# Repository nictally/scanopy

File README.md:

Hello, This is the repository for scanopy a smart air pollution monitoring system.

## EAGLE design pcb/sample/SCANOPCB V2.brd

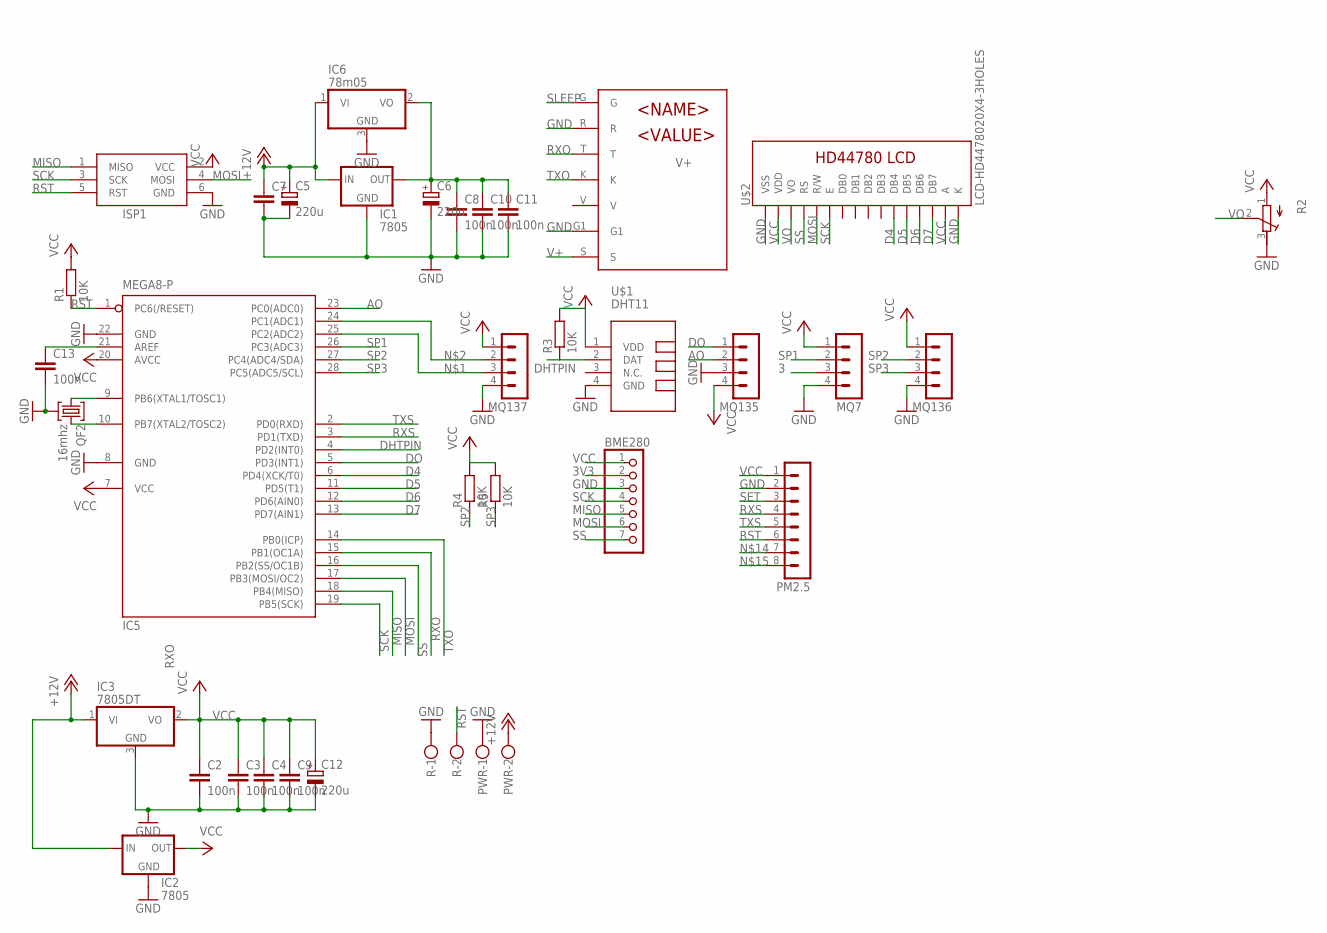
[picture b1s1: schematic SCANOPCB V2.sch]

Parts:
BME280: PINHD-1X7; 1X07
C2, C3, C4, C8, C9, C10, C11, C13: 100n; C1206
C5, C6, C12: 220u; E5-8,5
C7: C-EUC1206; C1206
IC1, IC2: 7805; 78XXL
IC3: 7805DT; TO252
IC5: MEGA8-P; DIL28-3
IC6: 78m05; TO252
ISP1: AVRISP-6; AVRISP
MQ7, MQ135, MQ136, MQ137: MA04-1
PM2.5: MA08-1
PWR: W237-102
QF2: 16mhz; HC49U
R: W237-102
R1, R3, R4, R5: 10K; R1206
R2: R-TRIMM64P; RTRIM64P
SIM7000: SIM7000
U$1: DHT11; TEMP-HUM-SENSOR-DHT11
U$2: LCD-HD4478020X4-3HOLES; LCD-20X4-3HOLES

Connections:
3: MQ7.3
3V3: BME280.2
+12V: C5.+, C7.1, IC1.IN, IC2.IN, IC3.1 (VI), IC6.1 (VI), PWR.2
AO: IC5.23 (PC0(ADC0)), MQ135.2
D4: IC5.6 (PD4(XCK/T0)), U$2.P$11 (DB4)
D5: IC5.11 (PD5(T1)), U$2.P$12 (DB5)
D6: IC5.12 (PD6(AIN0)), U$2.P$13 (DB6)
D7: IC5.13 (PD7(AIN1)), U$2.P$14 (DB7)
DHTPIN: IC5.4 (PD2(INT0)), R3.1, U$1.2 (DAT)
DO: IC5.5 (PD3(INT1)), MQ135.1
GND: BME280.3, C2.2, C3.2, C4.2, C5.-, C6.-, C7.2, C8.2, C9.2, C10.2, C11.2, C12.-, C13.2, IC1.GND, IC2.GND, IC3.3 (GND), IC5.8 (GND), IC5.22 (GND), IC6.3 (GND), ISP1.6 (GND), MQ7.4, MQ135.3, MQ136.4, MQ137.4, PM2.5.2, PWR.1, QF2.2, R.1, R2.3 (E), SIM7000.G1, SIM7000.R, U$1.4 (GND), U$2.P$1 (VSS), U$2.P$16 (K)
MISO: BME280.5, IC5.18 (PB4(MISO)), ISP1.1 (MISO)
MOSI: BME280.6, IC5.17 (PB3(MOSI/OC2)), ISP1.4 (MOSI), U$2.P$5 (R/W)
unnamed: IC5.25 (PC2(ADC2)), MQ137.3
unnamed: IC5.24 (PC1(ADC1)), MQ137.2
unnamed: C13.1, IC5.21 (AREF)
unnamed: IC5.9 (PB6(XTAL1/TOSC1)), QF2.1
unnamed: IC5.10 (PB7(XTAL2/TOSC2)), QF2.3
RST: IC5.1 (PC6(/RESET)), ISP1.5 (RST), PM2.5.6, R.2, R1.1
RXO: IC5.15 (PB1(OC1A)), SIM7000.T
RXS: IC5.3 (PD1(TXD)), PM2.5.4
SCK: BME280.4, IC5.19 (PB5(SCK)), ISP1.3 (SCK), U$2.P$6 (E)
SET: PM2.5.3
SLEEP: SIM7000.G
SP1: IC5.26 (PC3(ADC3)), MQ7.2
SP2: IC5.27 (PC4(ADC4/SDA)), MQ136.2, R4.1
SP3: IC5.28 (PC5(ADC5/SCL)), MQ136.3, R5.1
SS: BME280.7, IC5.16 (PB2(SS/OC1B)), U$2.P$4 (RS)
TXO: IC5.14 (PB0(ICP)), SIM7000.K
TXS: IC5.2 (PD0(RXD)), PM2.5.5
V+: C6.+, C8.1, C10.1, C11.1, IC1.OUT, IC6.2 (VO), SIM7000.S
VCC: BME280.1, C2.1, C3.1, C4.1, C9.1, C12.+, IC2.OUT, IC3.2 (VO), IC5.7 (VCC), IC5.20 (AVCC), ISP1.2 (VCC), MQ7.1, MQ135.4, MQ136.1, MQ137.1, PM2.5.1, R1.2, R2.1 (A), R3.2, R4.2, R5.2, U$1.1 (VDD), U$2.P$2 (VDD), U$2.P$15 (A)
VO: R2.2 (S), U$2.P$3 (VO)

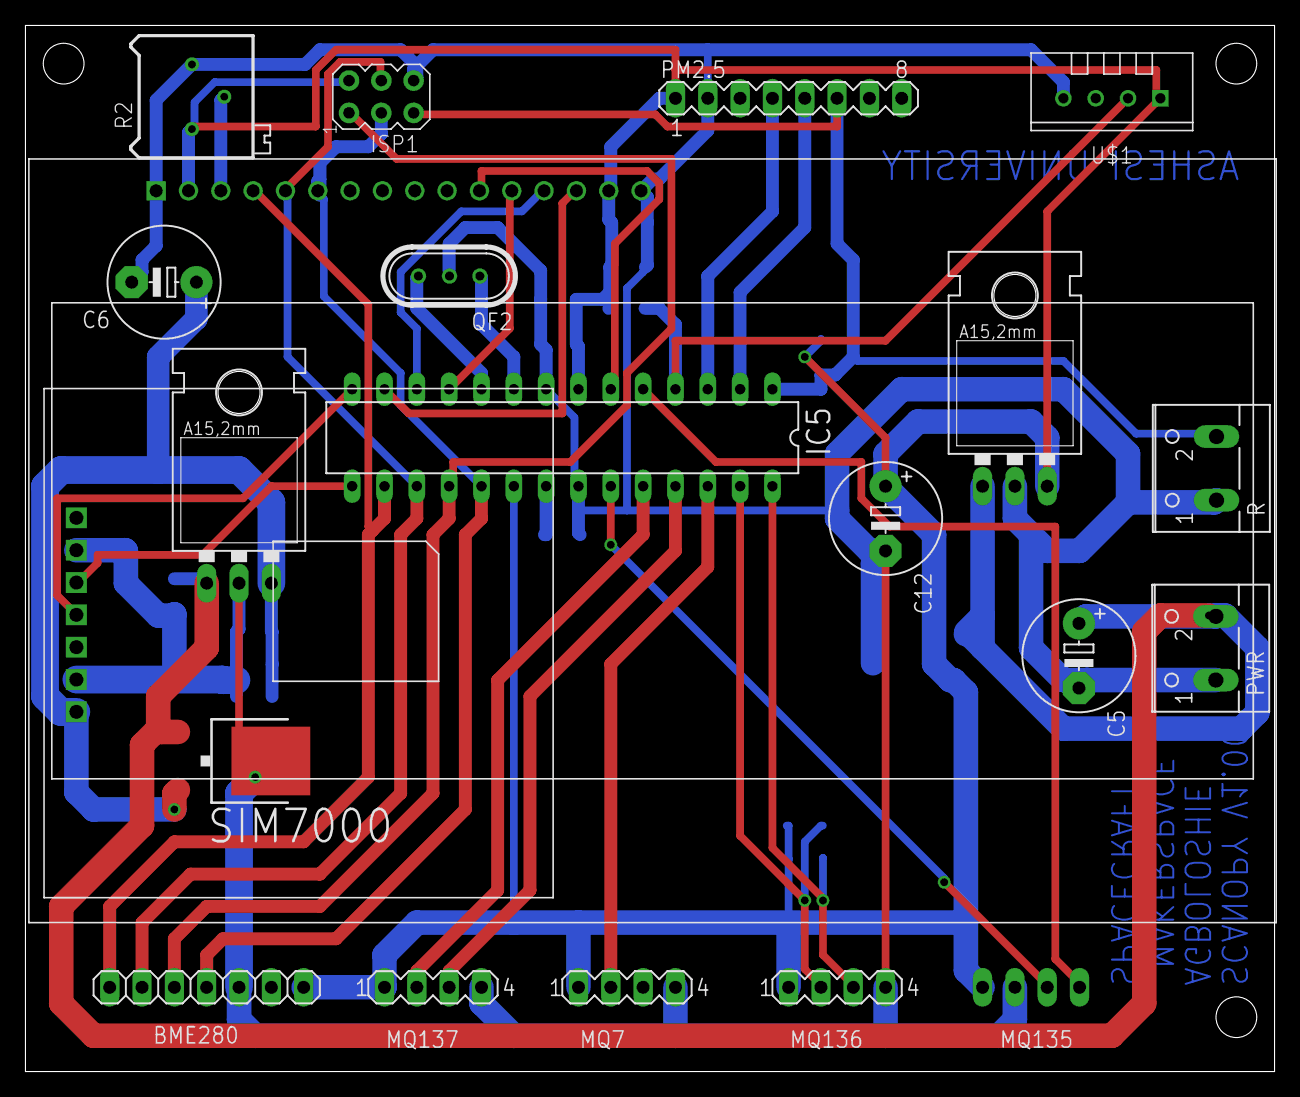
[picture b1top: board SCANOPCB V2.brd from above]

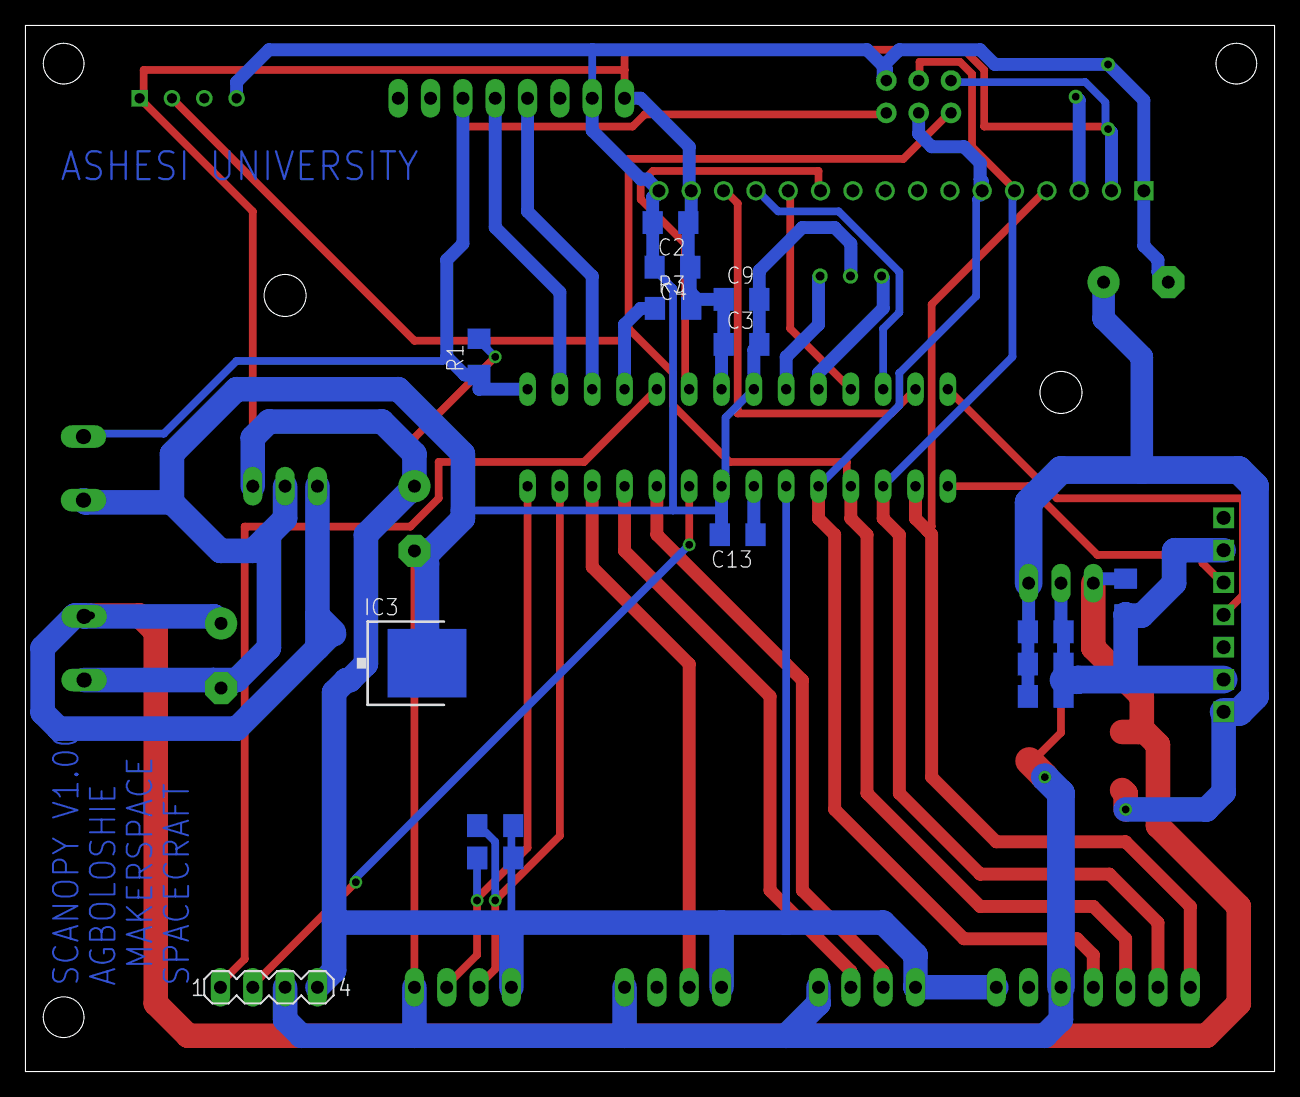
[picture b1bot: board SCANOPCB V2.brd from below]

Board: 2 copper layers, 98.1 x 82.2 mm, 35 parts (15 on the bottom side), 29 nets.

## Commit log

2019-01-25 Initial Pcb for Scanopy
2019-01-25 Updated arduino code
2019-01-25 Updated the topics
2019-01-25 Updated Readme FILE
2019-01-30 Added microcontroller
2019-01-30 WILLLIMS HEAD IS BIG
2019-01-30 Test push
2019-01-30 Updated sample PCB
2019-01-30 UPDATED CODE SAMPLE
2019-01-30 hannah's commit
2019-02-03 Update to software
2019-02-03 fixed bug for gsm setup
2019-02-08 GasSensor Class & Overall Update

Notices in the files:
parts and their libraries:
diy-modules: Released under the Creative Commons Attribution 4.0 International License: http://creativecommons.org/licenses/by/4.0
